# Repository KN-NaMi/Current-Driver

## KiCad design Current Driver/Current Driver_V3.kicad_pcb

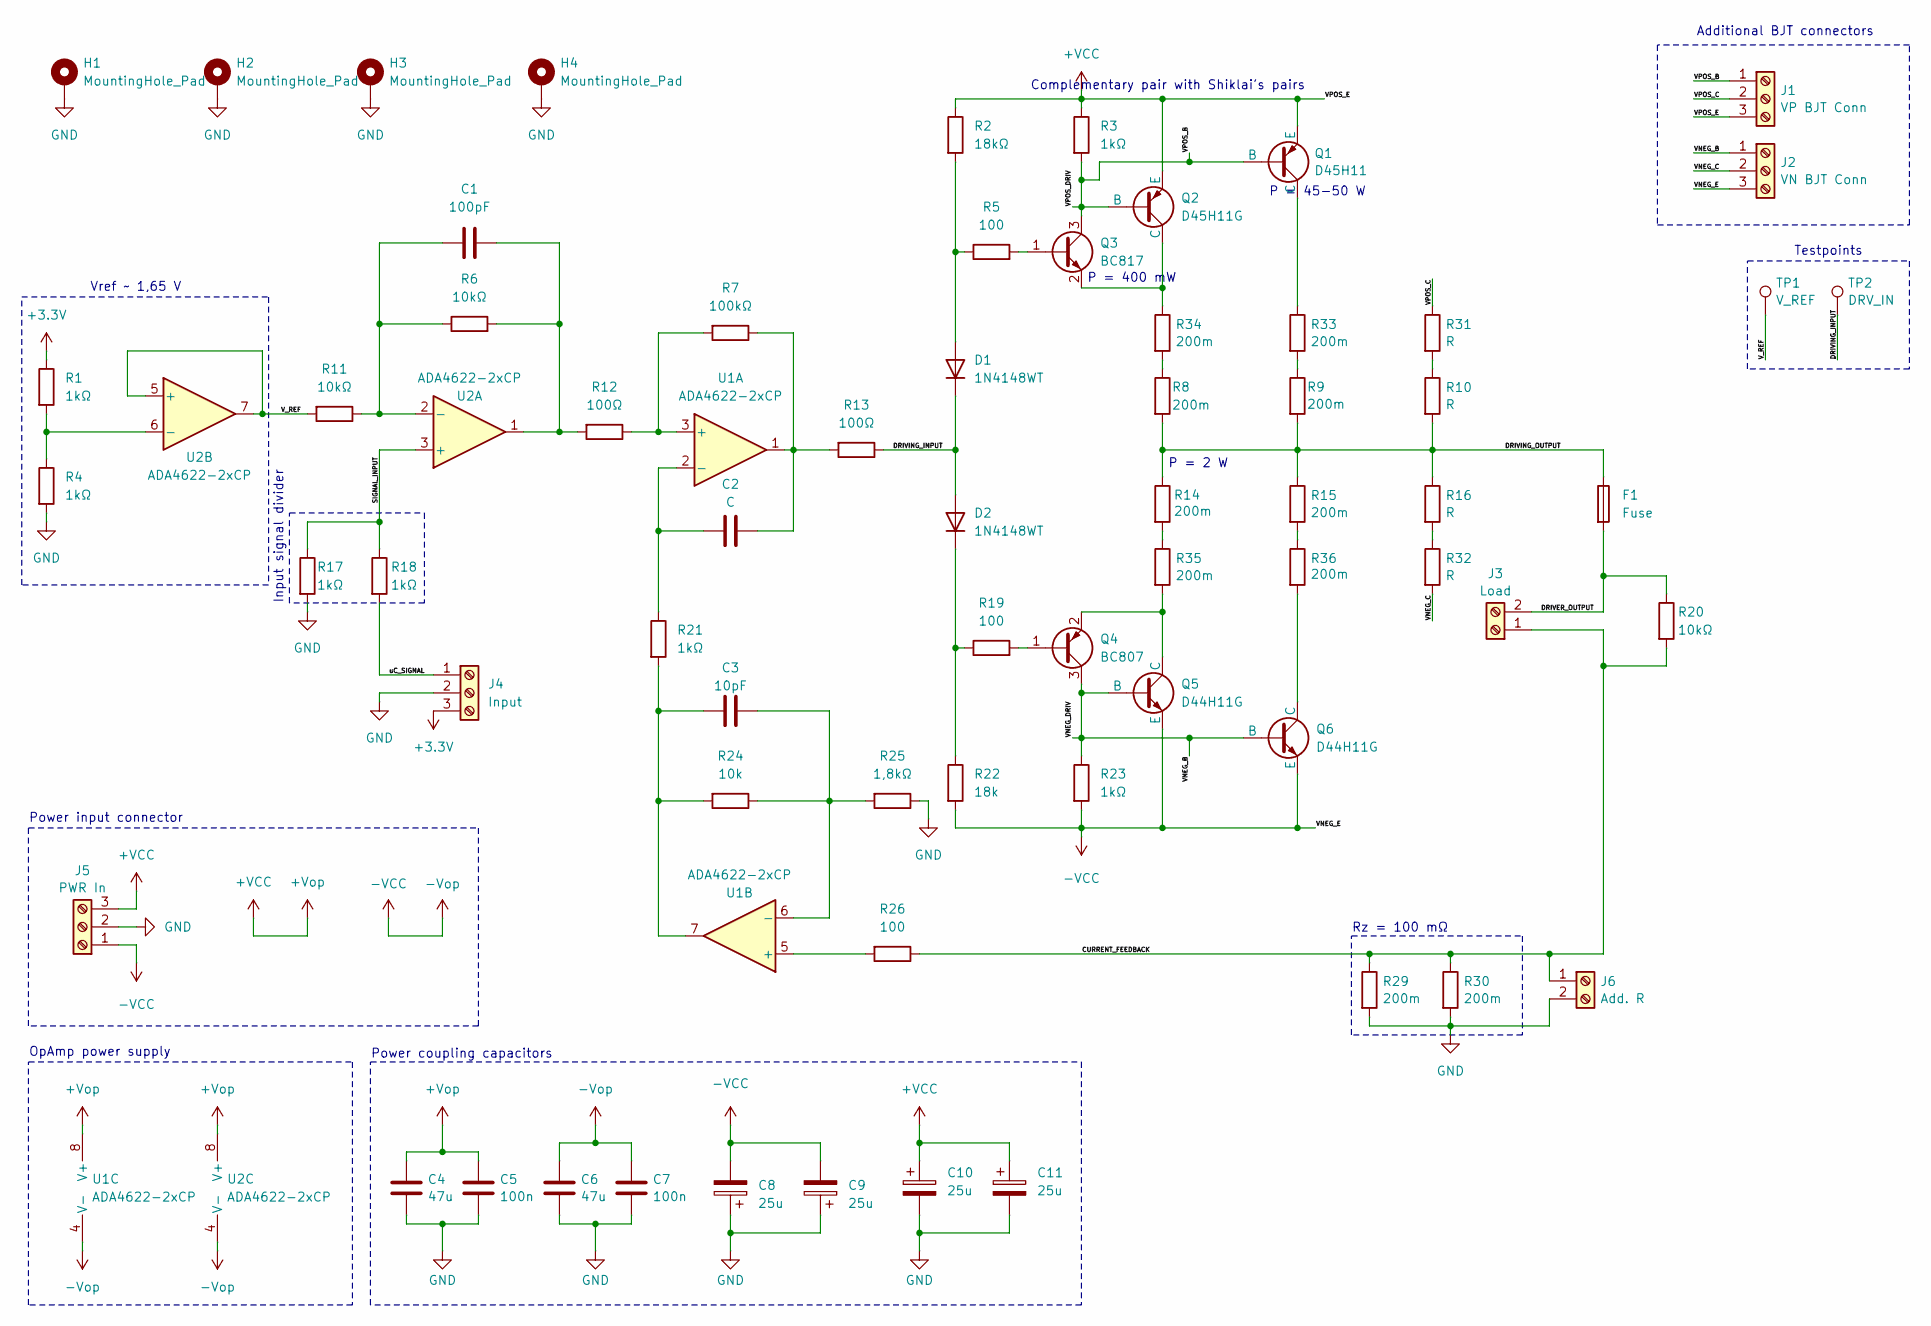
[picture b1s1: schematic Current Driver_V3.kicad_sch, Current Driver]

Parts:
C1: 100pF; C_0805_2012Metric_Pad1.18x1.45mm_HandSolder
C2: C; C_0805_2012Metric_Pad1.18x1.45mm_HandSolder
C3: 10pF; C_0805_2012Metric_Pad1.18x1.45mm_HandSolder
C4, C6: 47u; C_0805_2012Metric_Pad1.18x1.45mm_HandSolder
C5, C7: 100n; C_0805_2012Metric_Pad1.18x1.45mm_HandSolder
C8, C9, C10, C11: 25u; CP_Elec_6.3x7.7
D1, D2: 1N4148WT; D_SOD-523
F1: Fuse; 2410 FUSE
H1, H2, H3, H4: MountingHole_Pad; MountingHole_3.2mm_M3_DIN965_Pad_TopBottom
J1: VP BJT Conn; TerminalBlock_Xinya_XY308-2.54-3P_1x03_P2.54mm_Horizontal
J2: VN BJT Conn; TerminalBlock_Xinya_XY308-2.54-3P_1x03_P2.54mm_Horizontal
J3: Load; TerminalBlock_Xinya_XY308-2.54-2P_1x02_P2.54mm_Horizontal
J4: Input; TerminalBlock_Xinya_XY308-2.54-3P_1x03_P2.54mm_Horizontal
J5: PWR In; TerminalBlock_Xinya_XY308-2.54-3P_1x03_P2.54mm_Horizontal
J6: Add. R; TerminalBlock_Xinya_XY308-2.54-2P_1x02_P2.54mm_Horizontal
Q1: D45H11; D44H11G
Q2: D45H11G; D44H11G
Q3: BC817; SOT-23
Q4: BC807; SOT-23
Q5, Q6: D44H11G
R1, R3, R4, R17, R18, R21, R23: 1kΩ; R_0805_2012Metric_Pad1.20x1.40mm_HandSolder
R2: 18kΩ; R_0805_2012Metric_Pad1.20x1.40mm_HandSolder
R5, R19, R26: 100; R_0805_2012Metric_Pad1.20x1.40mm_HandSolder
R6, R11, R20: 10kΩ; R_0805_2012Metric_Pad1.20x1.40mm_HandSolder
R7: 100kΩ; R_0805_2012Metric_Pad1.20x1.40mm_HandSolder
R8, R9, R14, R15, R29, R30, R33, R34, R35, R36: 200m; R_2512_6332Metric_Pad1.40x3.35mm_HandSolder
R10, R16, R31, R32: R; R_2512_6332Metric_Pad1.40x3.35mm_HandSolder
R12, R13: 100Ω; R_0805_2012Metric_Pad1.20x1.40mm_HandSolder
R22: 18k; R_0805_2012Metric_Pad1.20x1.40mm_HandSolder
R24: 10k; R_0805_2012Metric_Pad1.20x1.40mm_HandSolder
R25: 1,8kΩ; R_0805_2012Metric_Pad1.20x1.40mm_HandSolder
TP1: V_REF; TestPoint_Loop_D2.60mm_Drill1.4mm_Beaded
TP2: DRV_IN; TestPoint_Loop_D2.60mm_Drill1.4mm_Beaded
U1, U2: ADA4622-2xCP; ADA4522

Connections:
+3.3V: J4.3, R1.1
+VCC: C4.1, C5.1, C10.1, C11.1, J1.3, J5.3, Q1.3 (E), Q2.3 (E), R2.1, R3.1, U1.8 (V+), U1.9 (V+), U2.8 (V+), U2.9 (V+)
-VCC: C6.1, C7.1, C8.2, C9.2, J2.3, J5.1, Q5.3 (E), Q6.3 (E), R22.2, R23.2, U1.4 (V-), U2.4 (V-)
/CURRENT_FEEDBACK: J3.1, J6.1, R20.2, R26.1, R29.1, R30.1
/DRIVER_OUTPUT: F1.2, J3.2, R20.1
/DRIVING_INPUT: D1.1 (K), D2.2 (A), R13.1, TP2.1
/DRIVING_OUTPUT: F1.1, R8.2, R9.2, R10.2, R14.1, R15.1, R16.1
/SIGNAL_INPUT: R17.1, R18.1, U2.3 (+)
/VNEG_B: J2.1, Q4.3 (C), Q5.2 (B), Q6.2 (B), R23.1
/VNEG_C: J2.2, R32.2
/VPOS_B: J1.1, Q1.2 (B), Q2.2 (B), Q3.3 (C), R3.2
/VPOS_C: J1.2, R31.1
/V_REF: R11.2, TP1.1, U2.5 (+), U2.7
/uC_SIGNAL: J4.1, R18.2
GND: C4.2, C5.2, C6.2, C7.2, C8.1, C9.1, C10.2, C11.2, H1.1, H2.1, H3.1, H4.1, J4.2, J5.2, J6.2, R4.2, R17.2, R25.1, R29.2, R30.2
unnamed: C1.2, R6.2, R12.2, U2.1
unnamed: C2.2, R7.1, R13.2, U1.1
unnamed: C3.1, R21.2, R24.2, U1.7
unnamed: D1.2 (A), R2.2, R5.1
unnamed: D2.1 (K), R19.1, R22.1
unnamed: Q1.1 (C), R33.1
unnamed: Q2.1 (C), Q3.2 (E), R34.1
unnamed: Q3.1 (B), R5.2
unnamed: Q4.1 (B), R19.2
unnamed: Q4.2 (E), Q5.1 (C), R35.2
unnamed: Q6.1 (C), R36.2
unnamed: R10.1, R31.2
unnamed: R14.2, R35.1
unnamed: R15.2, R36.1
unnamed: R16.2, R32.1
unnamed: R9.1, R33.2
unnamed: R8.1, R34.2
unnamed: R7.2, R12.1, U1.3 (+)
unnamed: C2.1, R21.1, U1.2 (-)
unnamed: R26.2, U1.5 (+)
unnamed: C3.2, R24.1, R25.2, U1.6 (-)
unnamed: C1.1, R6.1, R11.1, U2.2 (-)
unnamed: R1.2, R4.1, U2.6 (-)

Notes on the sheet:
Complementary pair with Shiklai's pairs
Input signal divider
Power input connector
Power coupling capacitors
OpAmp power supply
P = 400 mW
Testpoints
P = 45-50 W
P = 2 W
Additional BJT connectors
Rz = 100 mΩ
Vref ~ 1,65 V

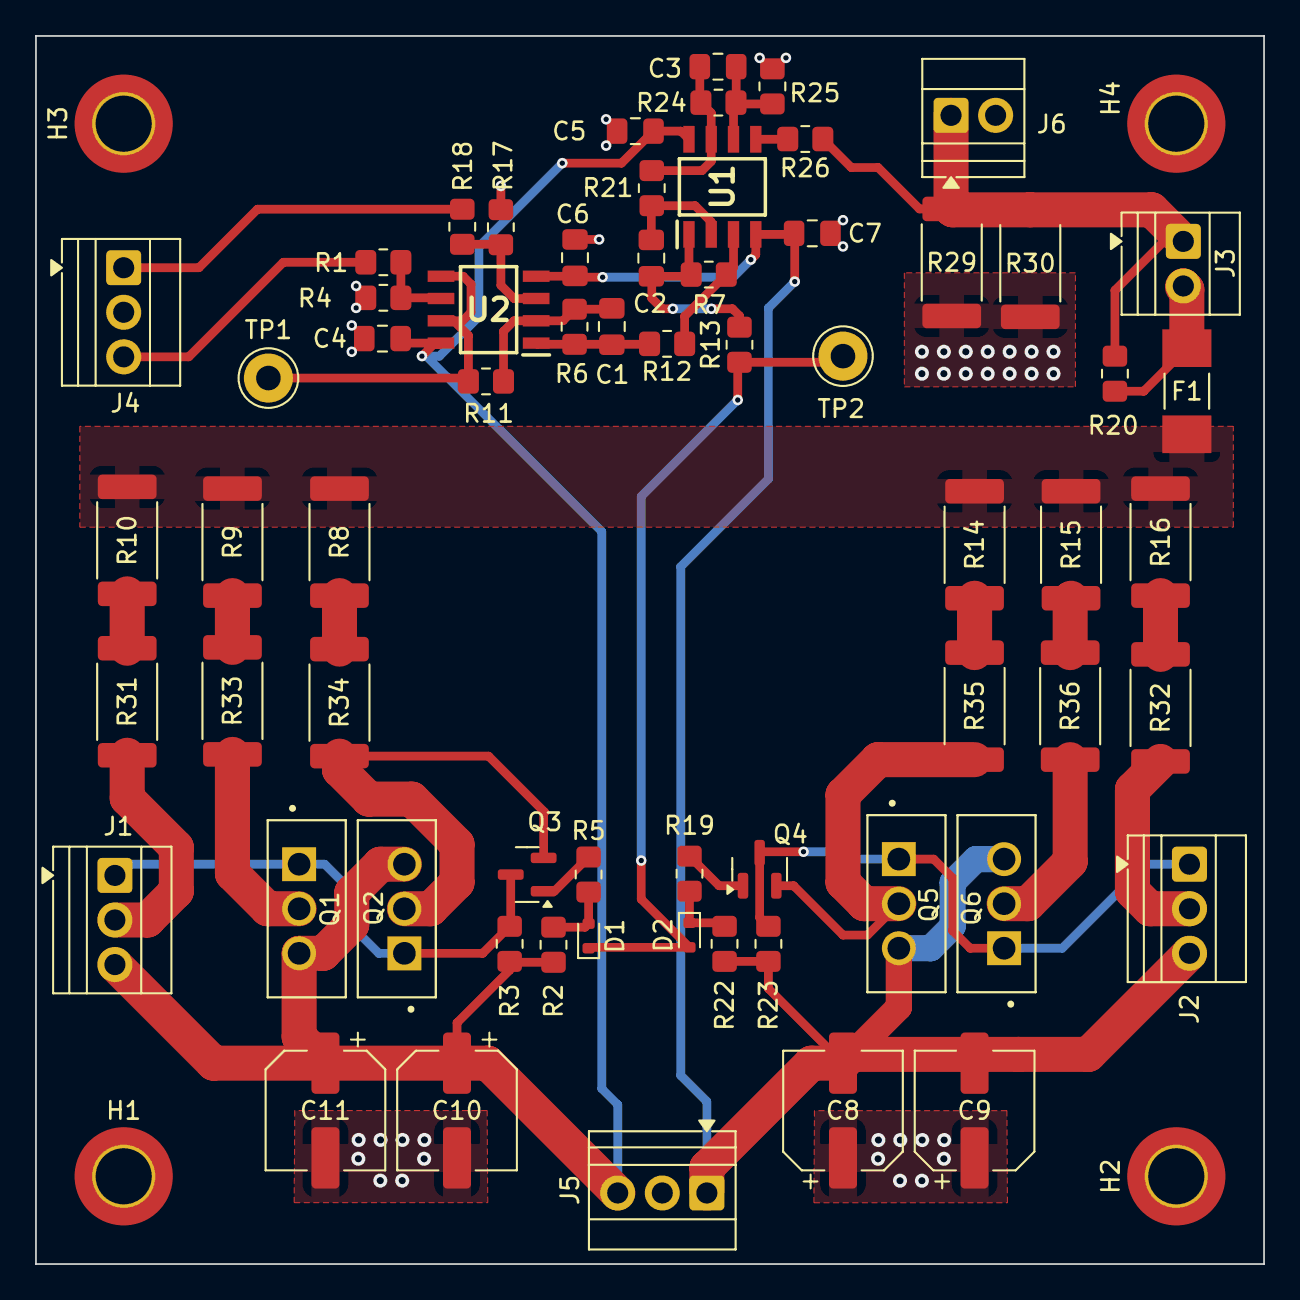
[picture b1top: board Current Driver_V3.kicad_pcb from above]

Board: 2 copper layers, 70.0 x 70.0 mm, 68 parts (0 on the bottom side), 38 nets.

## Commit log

2025-07-31 Stary schmat
    Dodano stary schemat przeniesiony do KiCada
2025-10-04 Clean Schematic
2025-11-01 Add Spice simulation
2025-11-14 edit schamatic update
2025-11-15 Check & Edit Schematic
2025-11-16 schematic update
2025-11-16 Edit Schematic
    Added opAmp for stable reference voltage. Anotated schematic
2025-11-21 Minor Edit PCB
2025-12-15 PCB_wersja1
2025-12-29 PCB_v2
2026-02-19 PCB V3
2026-02-19 Update PCB
